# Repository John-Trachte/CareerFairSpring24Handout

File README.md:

### CareerFairSpring24Handout
Design files and code for boards to be handed out at the Spring '24 career fair.

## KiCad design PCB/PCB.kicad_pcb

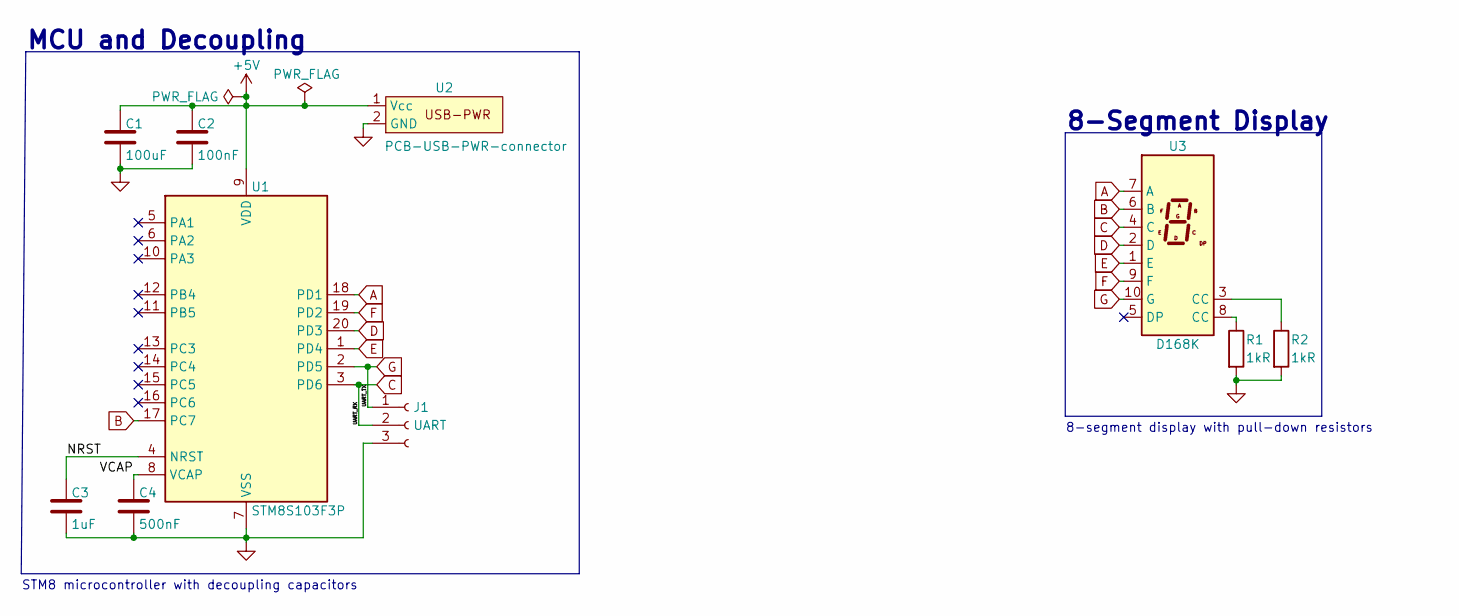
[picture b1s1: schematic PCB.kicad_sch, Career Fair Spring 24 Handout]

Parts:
C1: 100uF; C_1206_3216Metric
C2: 100nF; C_0603_1608Metric
C3: 1uF; C_0603_1608Metric
C4: 500nF; C_0805_2012Metric
J1: UART; FanPinHeader_1x03_P2.54mm_Vertical
R1, R2: 1kR; R_0402_1005Metric
U1: STM8S103F3P; TSSOP-20_4.4x6.5mm_P0.65mm
U2: PCB-USB-PWR-connector
U3: D168K; D1X8K

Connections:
+5V: C1.1, C2.1, U1.9 (VDD), U2.1 (Vcc)
/NRST: C3.1, U1.4 (NRST)
/VCAP: C4.1, U1.8 (VCAP)
A: U1.18 (PD1), U3.7 (A)
B: U1.17 (PC7), U3.6 (B)
C: J1.2, U1.3 (PD6), U3.4 (C)
D: U1.20 (PD3), U3.2 (D)
E: U1.1 (PD4), U3.1 (E)
F: U1.19 (PD2), U3.9 (F)
G: J1.1, U1.2 (PD5), U3.10 (G)
GND: C1.2, C2.2, C3.2, C4.2, J1.3, R1.2, R2.2, U1.7 (VSS), U2.2 (GND)
unnamed: R1.1, U3.8 (CC)
unnamed: R2.1, U3.3 (CC)

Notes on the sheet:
8-Segment Display
STM8 microcontroller with decoupling capacitors
MCU and Decoupling
8-segment display with pull-down resistors

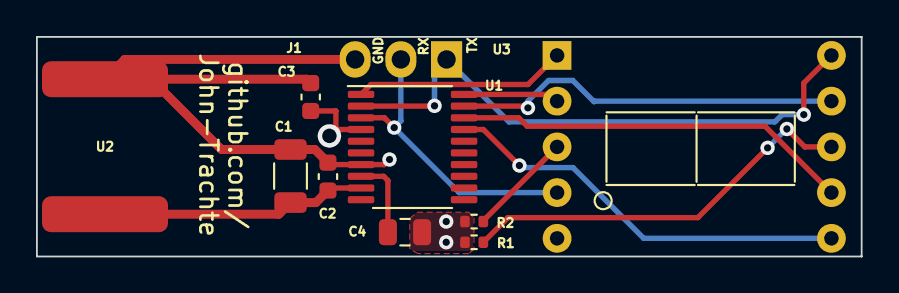
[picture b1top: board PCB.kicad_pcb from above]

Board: 2 copper layers, 45.8 x 12.2 mm, 10 parts (0 on the bottom side), 13 nets.

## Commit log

2023-11-15 Initial commit, include major parts
2023-11-15 Active low note
2024-01-08 Documentation and citations for selected MCU
2024-01-09 PCB schematic first draft
2024-01-09 Project restructure
2024-01-09 Custom USB power connector
2024-01-09 Rev 0.11 of schematic, rev 0.1 of layout
2024-01-09 Add pin defenitions file
2024-01-10 PCB revision 0.11: correct decoupling capacitors, change IO routing, Schematic revision 0.12: change IO routing
2024-01-10 Update pinout to reflect PCB changes
2024-01-10 PCB modifications
2024-01-10 Add sequence diagram
2024-01-10 Create main file
2024-01-12 Reflect MCU on dev board with original pinout
2024-01-16 Update backups
2024-01-16 Add lexer files and references
2024-01-16 Break out NRST for programming
2024-01-16 Add joke file
2024-01-16 Add gitignore
2024-01-16 Move lexer files, fix references in main.c
2024-01-19 Add Makefile
2024-01-19 Refactor to more specific project structure
2024-01-19 Update project structure
2024-01-23 Support testing in Makefile
2024-01-25 Add GPIO test file
2024-01-26 Rename/clean up file
2024-01-26 Encoding for GPIO driver
2024-01-26 Format CC variable
2024-01-30 Add UART header
2024-01-31 Generate gerbers for first edition
